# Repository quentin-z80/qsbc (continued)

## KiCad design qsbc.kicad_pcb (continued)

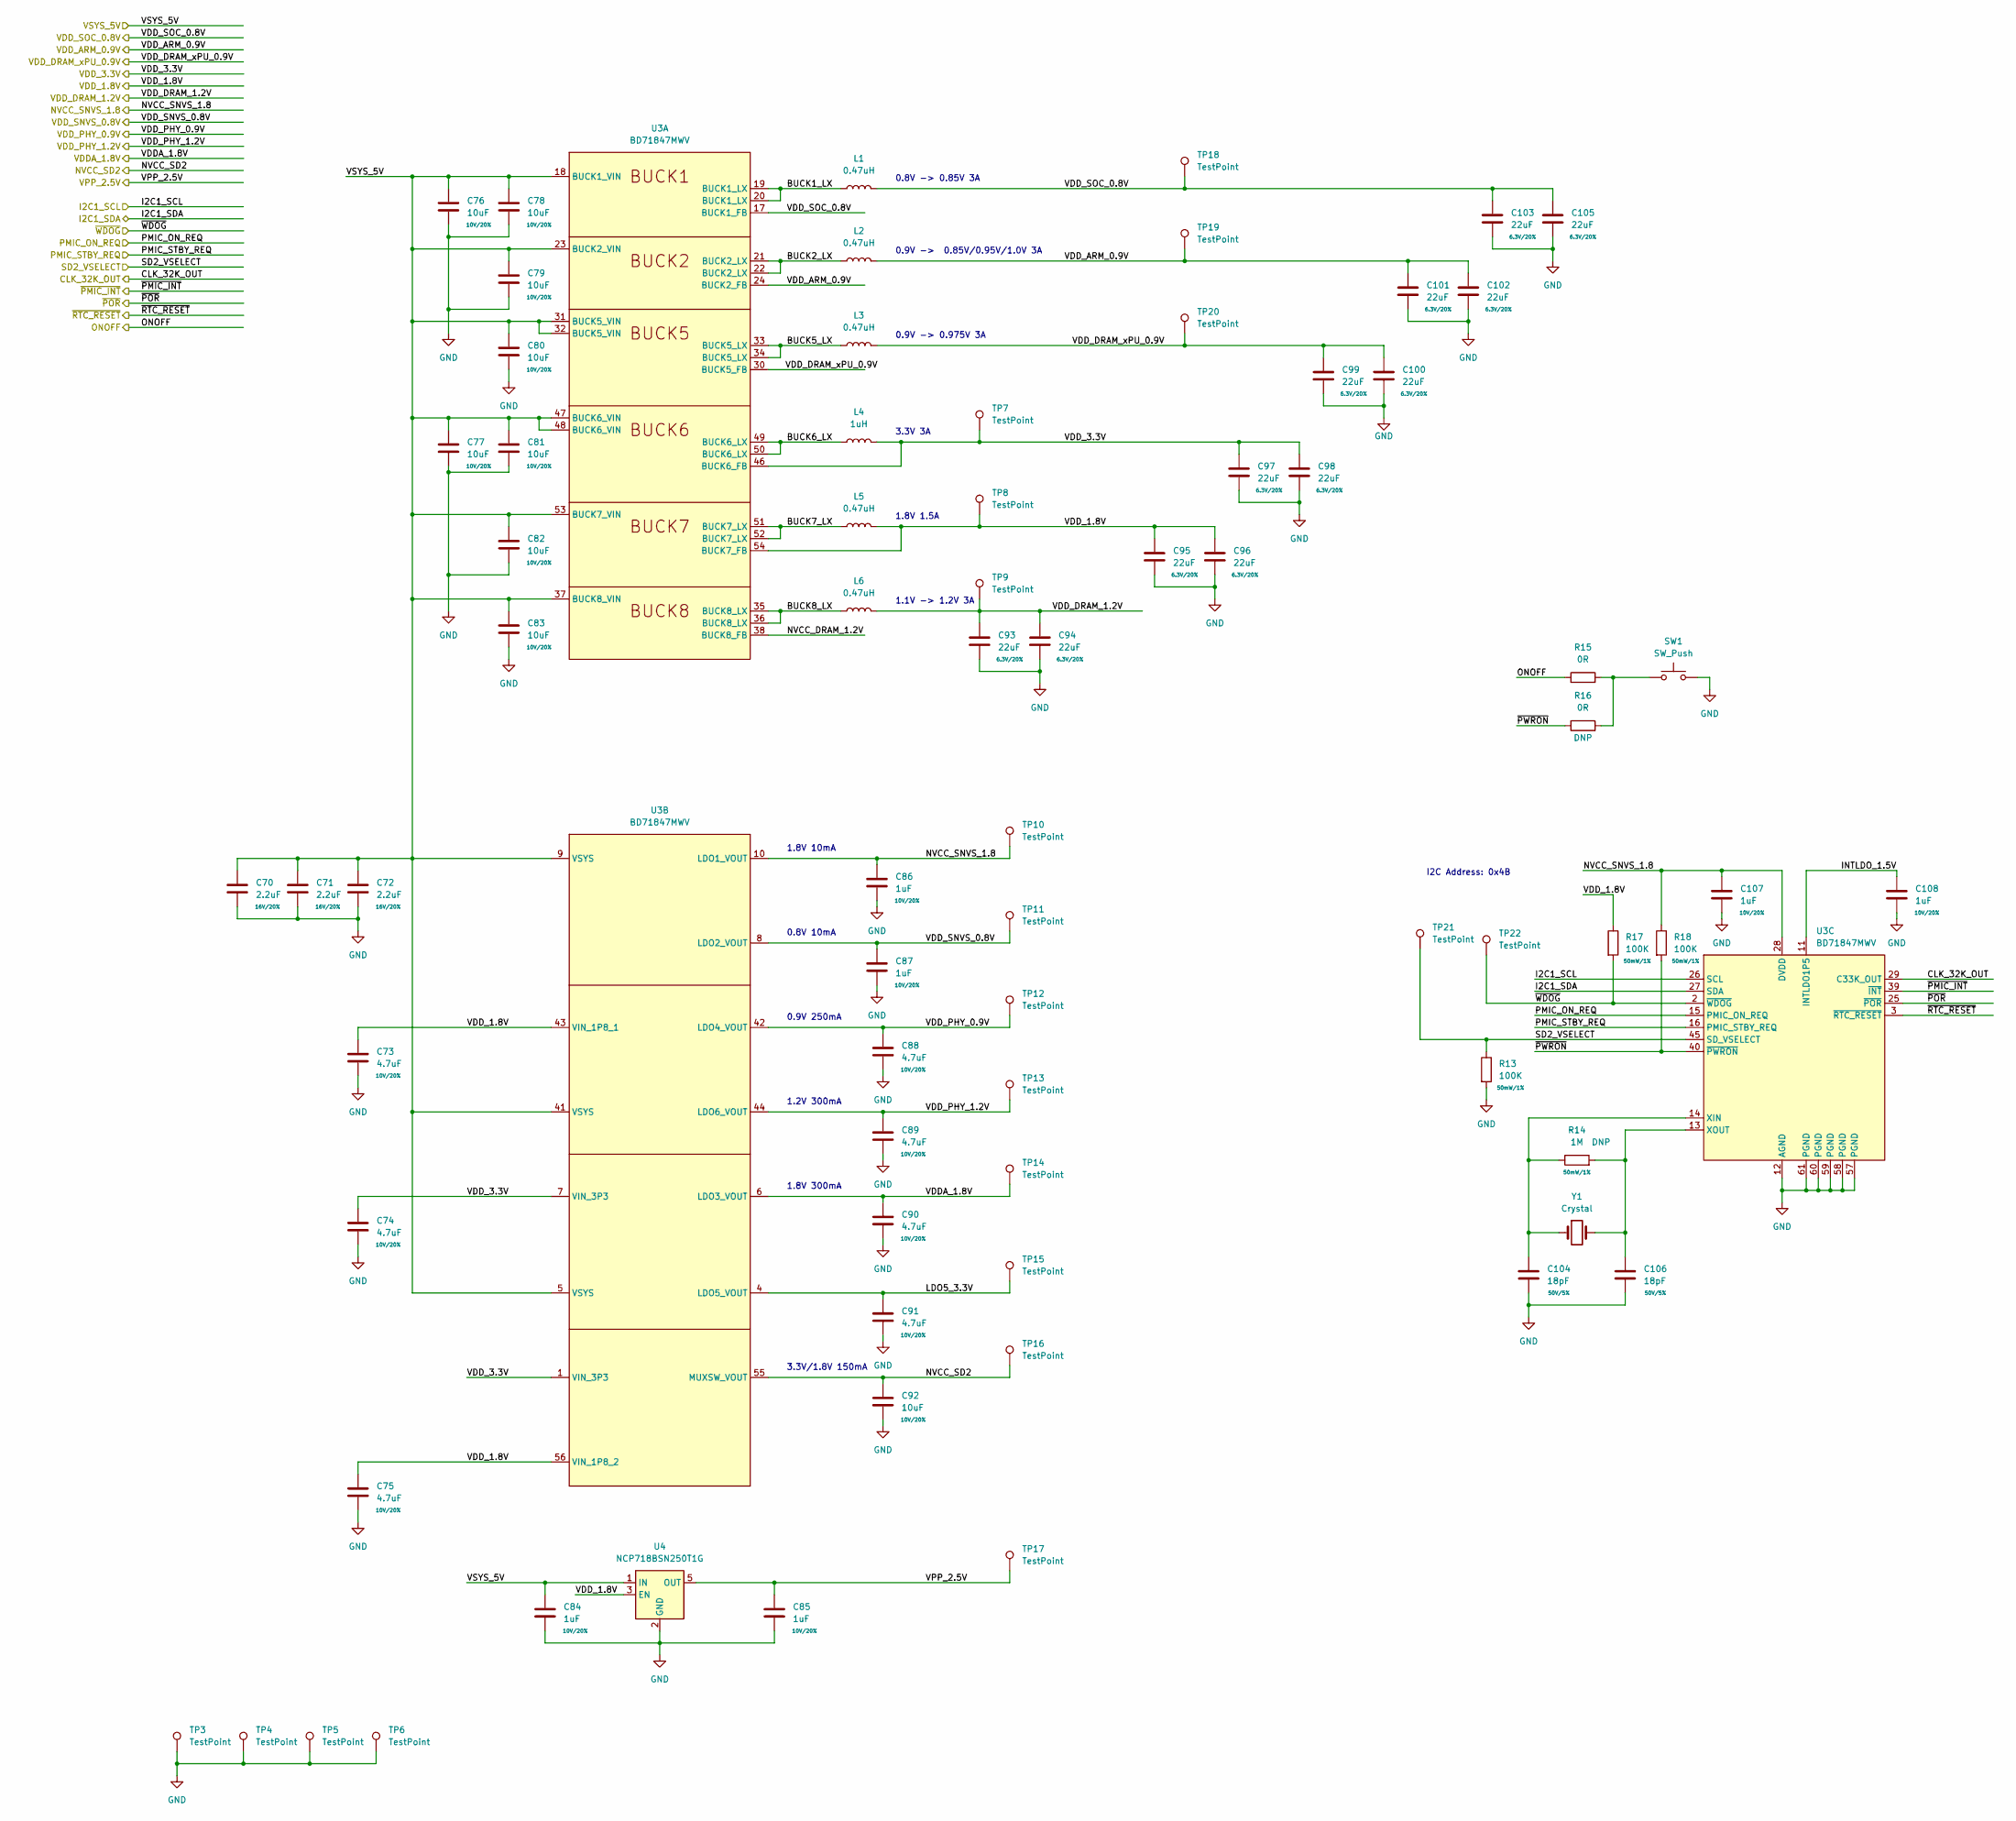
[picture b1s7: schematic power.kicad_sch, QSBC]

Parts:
C70, C71, C72: 2.2uF; C_0402_1005Metric; Rating 16V/20%
C73, C74, C75, C88, C89, C90, C91: 4.7uF; C_0402_1005Metric; Rating 10V/20%
C76, C77, C78, C79, C80, C81, C82, C83, C92: 10uF; C_0603_1608Metric; Rating 10V/20%
C84, C85, C86, C87, C107, C108: 1uF; C_0402_1005Metric; Rating 10V/20%
C93, C94, C95, C96, C97, C98, C99, C100, C101, C102, C103, C105: 22uF; C_0603_1608Metric; Rating 6.3V/20%
C104, C106: 18pF; C_0402_1005Metric; Rating 50V/5%
L1, L2, L3, L5, L6: 0.47uH; L_1008_2520Metric
L4: 1uH; L_1008_2520Metric
R13, R17, R18: 100K; R_0402_1005Metric; Rating 50mW/1%
R14: 1M; R_0402_1005Metric; Rating 50mW/1%
R15, R16: 0R; R_0402_1005Metric
SW1: SW_Push; SW_Tactile_SPST_Angled_PTS645Vx58-2LFS
TP3, TP4, TP5, TP6, TP7, TP8, TP9, TP10, TP11, TP12, TP13, TP14, TP15, TP16, TP17, TP18, TP19, TP20, TP21, TP22: TestPoint; TestPoint_Pad_D1.0mm
U3: BD71847MWV; UQFN56BV7070
U4: NCP718BSN250T1G; SOT-23-5
Y1: Crystal; Crystal_SMD_2012-2Pin_2.0x1.2mm

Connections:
/DDR/VDD_DRAM_1.2V: C93.1, C94.1, L6.2, TP9.1; also elsewhere on the board
/DDR/VPP_2.5V: C85.1, TP17.1, U4.5 (OUT); also elsewhere on the board
/Misc/CLK_32K_OUT: U3.29 (C33K_OUT); also elsewhere on the board
/Misc/NVCC_SNVS_1.8V: C86.1, C107.1, R18.1, TP10.1, U3.10 (LDO1_VOUT), U3.28 (DVDD); also elsewhere on the board
/Misc/ONOFF: R15.1; also elsewhere on the board
/Misc/PMIC_ON_REQ: U3.15 (PMIC_ON_REQ); also elsewhere on the board
/Misc/PMIC_STBY_REQ: U3.16 (PMIC_STBY_REQ); also elsewhere on the board
/Misc/VDD_SNVS_0.8V: C87.1, TP11.1, U3.8 (LDO2_VOUT); also elsewhere on the board
/Misc/~POR: U3.25 (~POR); also elsewhere on the board
/Misc/~RTC_RESET: U3.3 (~RTC_RESET); also elsewhere on the board
/Peripherals/I2C1_SCL: U3.26 (SCL); also elsewhere on the board
/Peripherals/I2C1_SDA: U3.27 (SDA); also elsewhere on the board
/Peripherals/SD2_VSELECT: R13.1, TP21.1, U3.45 (SD_VSELECT); also elsewhere on the board
/Peripherals/~PMIC_INT: U3.39 (~INT); also elsewhere on the board
/Power/BUCK1_LX: L1.1, U3.19 (BUCK1_LX), U3.20 (BUCK1_LX)
/Power/BUCK2_LX: L2.1, U3.21 (BUCK2_LX), U3.22 (BUCK2_LX)
/Power/BUCK5_LX: L3.1, U3.33 (BUCK5_LX), U3.34 (BUCK5_LX)
/Power/BUCK6_LX: L4.1, U3.49 (BUCK6_LX), U3.50 (BUCK6_LX)
/Power/BUCK7_LX: L5.1, U3.51 (BUCK7_LX), U3.52 (BUCK7_LX)
/Power/BUCK8_LX: L6.1, U3.35 (BUCK8_LX), U3.36 (BUCK8_LX)
/Power/INTLDO_1.5V: C108.1, U3.11 (INTLDO1P5)
/Power/LDO5_3.3V: C91.1, TP15.1, U3.4 (LDO5_VOUT)
/Power/NVCC_DRAM_1.2V: U3.38 (BUCK8_FB)
/Power/NVCC_SD2: C92.1, TP16.1, U3.55 (MUXSW_VOUT); also elsewhere on the board
/Power/VDDA_1.8V: C90.1, TP14.1, U3.6 (LDO3_VOUT); also elsewhere on the board
/Power/VDD_ARM_0.9V: C101.1, C102.1, L2.2, TP19.1, U3.24 (BUCK2_FB); also elsewhere on the board
/Power/VDD_DRAM_xPU_0.9V: C99.1, C100.1, L3.2, TP20.1, U3.30 (BUCK5_FB); also elsewhere on the board
/Power/VDD_PHY_0.9V: C88.1, TP12.1, U3.42 (LDO4_VOUT); also elsewhere on the board
/Power/VDD_PHY_1.2V: C89.1, TP13.1, U3.44 (LDO6_VOUT); also elsewhere on the board
/Power/VDD_SOC_0.8V: C103.1, C105.1, L1.2, TP18.1, U3.17 (BUCK1_FB); also elsewhere on the board
/Power/VSYS_5V: C70.1, C71.1, C72.1, C76.1, C77.1, C78.1, C79.1, C80.1, C81.1, C82.1, C83.1, C84.1, U3.5 (VSYS), U3.9 (VSYS), U3.18 (BUCK1_VIN), U3.23 (BUCK2_VIN), U3.31 (BUCK5_VIN), U3.32 (BUCK5_VIN), U3.37 (BUCK8_VIN), U3.41 (VSYS), U3.47 (BUCK6_VIN), U3.48 (BUCK6_VIN), U3.53 (BUCK7_VIN), U4.1 (IN); also elsewhere on the board
/Power/~PWRON: R16.1, R18.2, U3.40 (~PWRON)
/Power/~WDOG: R17.2, TP22.1, U3.2 (~WDOG)
GND: C70.2, C71.2, C72.2, C73.2, C74.2, C75.2, C76.2, C77.2, C78.2, C79.2, C80.2, C81.2, C82.2, C83.2, C84.2, C85.2, C86.2, C87.2, C88.2, C89.2, C90.2, C91.2, C92.2, C93.2, C94.2, C95.2, C96.2, C97.2, C98.2, C99.2, C100.2, C101.2, C102.2, C103.2, C104.2, C105.2, C106.2, C107.2, C108.2, R13.2, SW1.2, TP3.1, TP4.1, TP5.1, TP6.1, U3.12 (AGND), U3.57 (PGND), U3.58 (PGND), U3.59 (PGND), U3.60 (PGND), U3.61 (PGND), U4.2 (GND); also elsewhere on the board
unnamed: C104.1, R14.1, U3.14 (XIN), Y1.1
unnamed: C106.1, R14.2, U3.13 (XOUT), Y1.2
unnamed: R15.2, R16.2, SW1.1
VDD_1.8V: C73.1, C75.1, C95.1, C96.1, L5.2, R17.1, TP8.1, U3.43 (VIN_1P8_1), U3.54 (BUCK7_FB), U3.56 (VIN_1P8_2), U4.3 (EN); also elsewhere on the board
VDD_3.3V: C74.1, C97.1, C98.1, L4.2, TP7.1, U3.1 (VIN_3P3), U3.7 (VIN_3P3), U3.46 (BUCK6_FB); also elsewhere on the board

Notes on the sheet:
0.8V 10mA
1.2V 300mA
0.9V 250mA
I2C Address: 0x4B
0.9V -> 0.85V/0.95V/1.0V 3A
3.3V 3A
0.9V -> 0.975V 3A
1.8V 300mA
1.8V 1.5A
1.8V 10mA
3.3V/1.8V 150mA
1.1V -> 1.2V 3A
0.8V -> 0.85V 3A

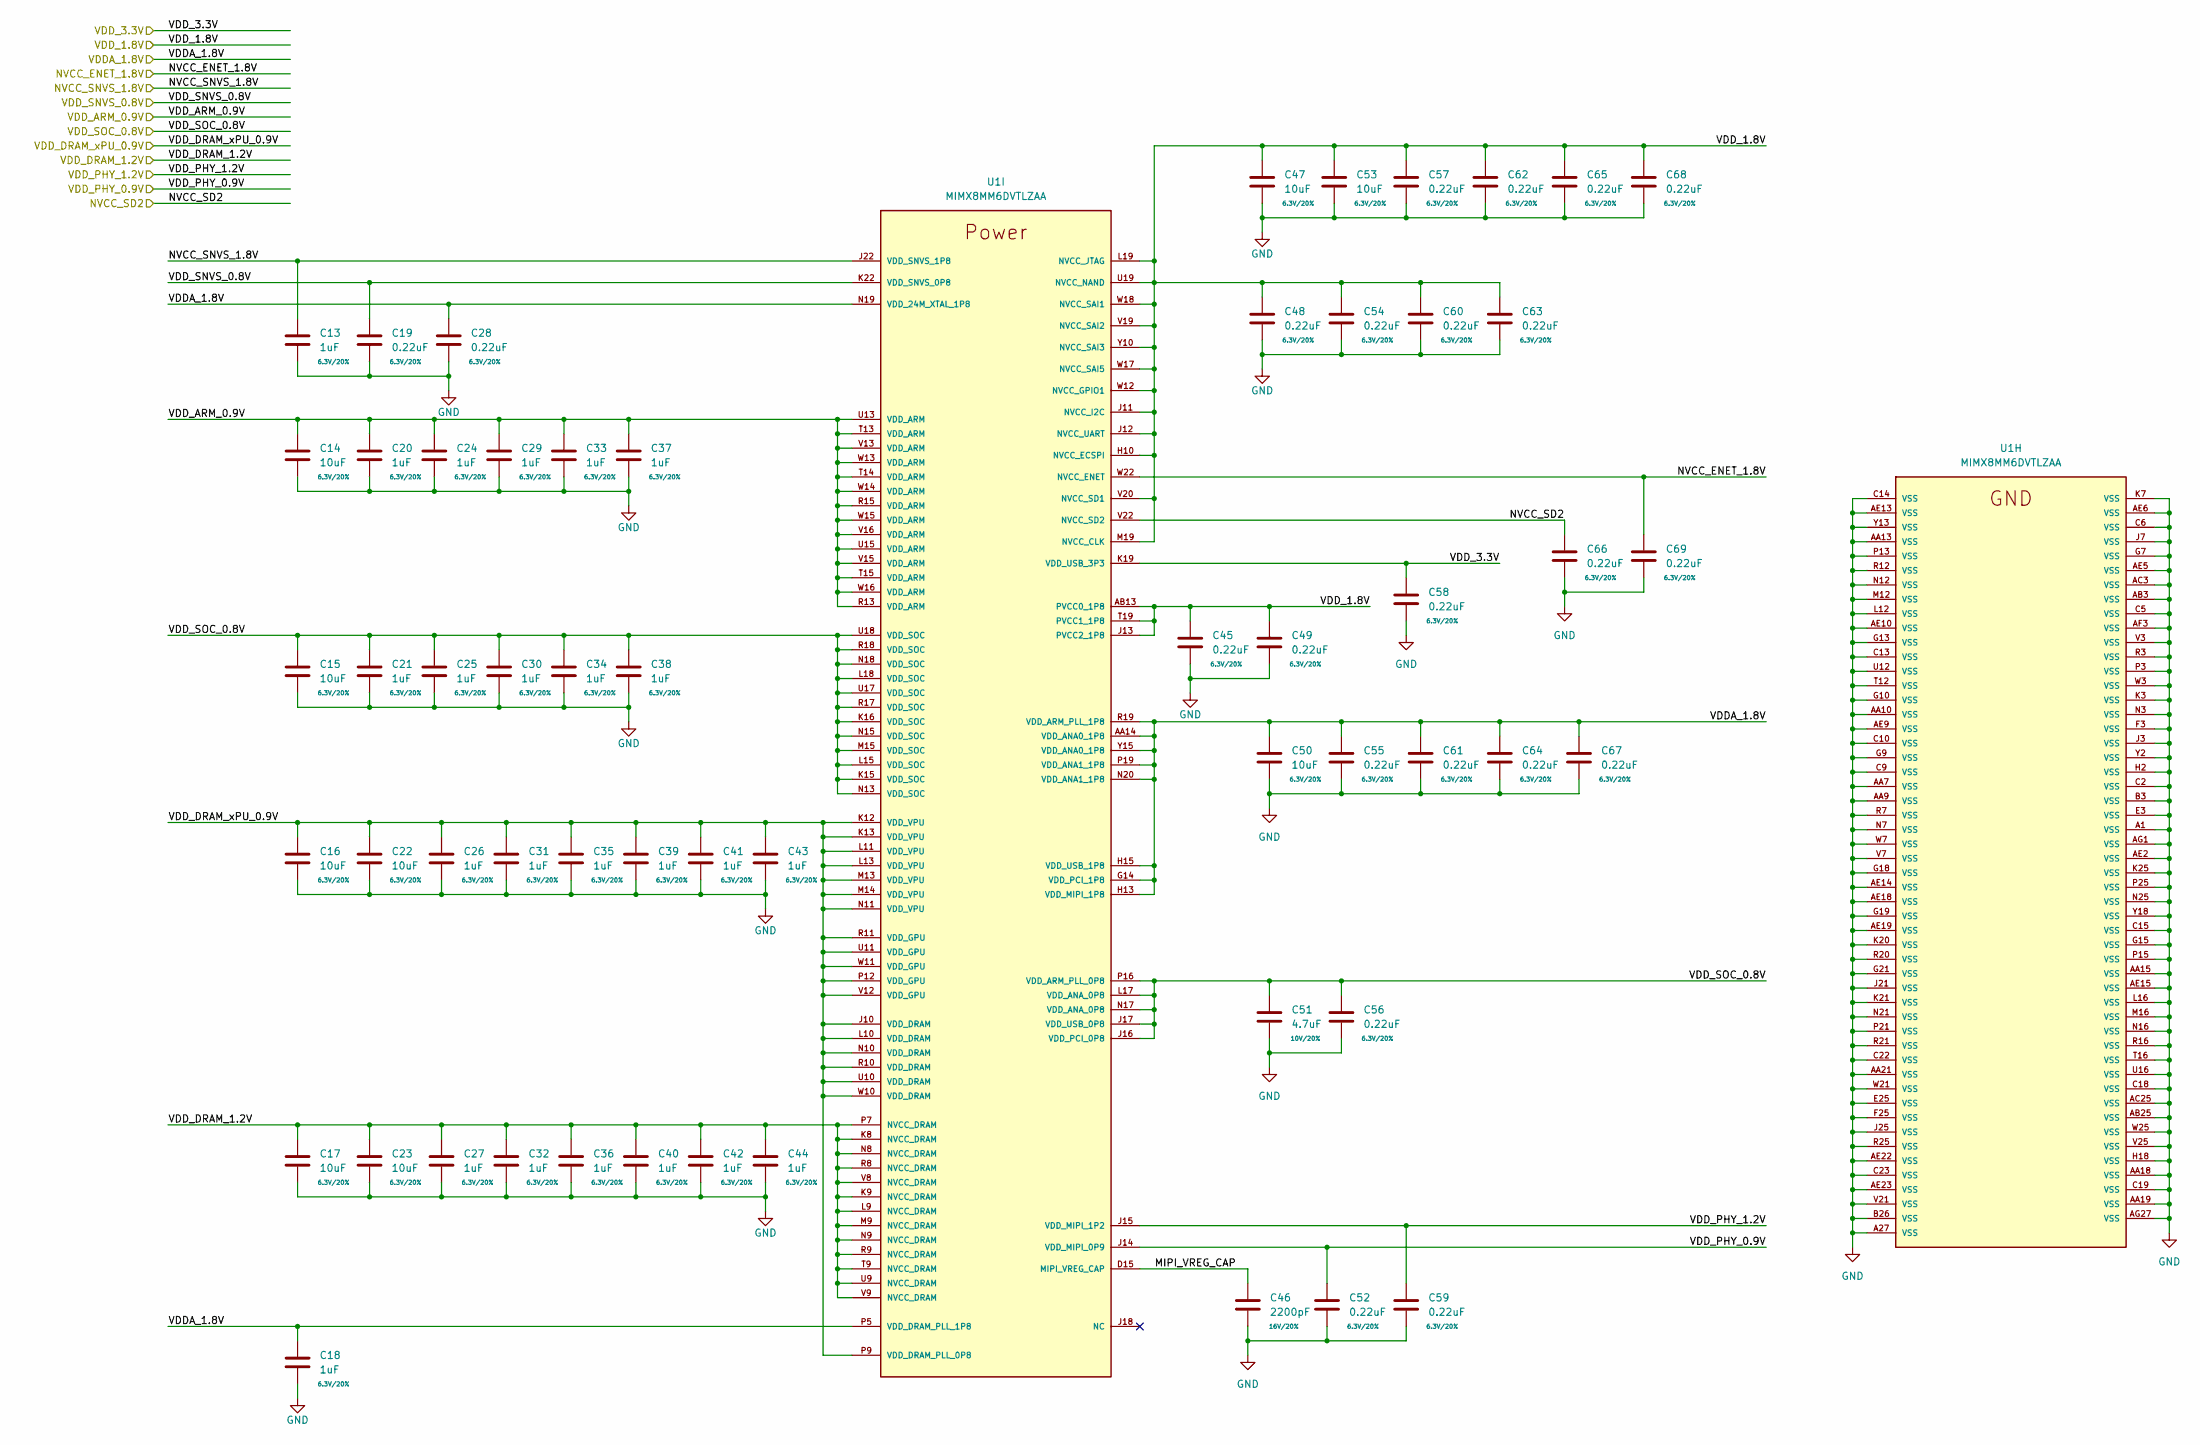
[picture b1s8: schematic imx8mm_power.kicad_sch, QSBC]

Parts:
C13, C18, C20, C21, C24, C25, C26, C27, C29, C30, C31, C32, C33, C34, C35, C36, C37, C38, C39, C40, C41, C42, C43, C44: 1uF; C_0201_0603Metric; Rating 6.3V/20%
C14, C15, C16, C17, C22, C23, C47, C50, C53: 10uF; C_0402_1005Metric; Rating 6.3V/20%
C19, C28, C45, C48, C49, C52, C54, C55, C56, C57, C58, C59, C60, C61, C62, C63, C64, C65, C66, C67, C68, C69: 0.22uF; C_0201_0603Metric; Rating 6.3V/20%
C46: 2200pF; C_0402_1005Metric; Rating 16V/20%
C51: 4.7uF; C_0402_1005Metric; Rating 10V/20%
U1: MIMX8MM6DVTLZAA; SOT1967-1

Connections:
/DDR/VDD_DRAM_1.2V: C17.1, C23.1, C27.1, C32.1, C36.1, C40.1, C42.1, C44.1, U1.K8 (NVCC_DRAM), U1.K9 (NVCC_DRAM), U1.L9 (NVCC_DRAM), U1.M9 (NVCC_DRAM), U1.N8 (NVCC_DRAM), U1.N9 (NVCC_DRAM), U1.P7 (NVCC_DRAM), U1.R8 (NVCC_DRAM), U1.R9 (NVCC_DRAM), U1.T9 (NVCC_DRAM), U1.U9 (NVCC_DRAM), U1.V8 (NVCC_DRAM), U1.V9 (NVCC_DRAM); also elsewhere on the board
/Ethernet/NVCC_ENET_1.8V: C69.1, U1.W22 (NVCC_ENET); also elsewhere on the board
/Misc/NVCC_SNVS_1.8V: C13.1, U1.J22 (VDD_SNVS_1P8); also elsewhere on the board
/Misc/VDD_SNVS_0.8V: C19.1, U1.K22 (VDD_SNVS_0P8); also elsewhere on the board
/Power/NVCC_SD2: C66.1, U1.V22 (NVCC_SD2); also elsewhere on the board
/Power/VDDA_1.8V: C18.1, C28.1, C50.1, C55.1, C61.1, C64.1, C67.1, U1.AA14 (VDD_ANA0_1P8), U1.G14 (VDD_PCI_1P8), U1.H13 (VDD_MIPI_1P8), U1.H15 (VDD_USB_1P8), U1.N19 (VDD_24M_XTAL_1P8), U1.N20 (VDD_ANA1_1P8), U1.P5 (VDD_DRAM_PLL_1P8), U1.P19 (VDD_ANA1_1P8), U1.R19 (VDD_ARM_PLL_1P8), U1.Y15 (VDD_ANA0_1P8); also elsewhere on the board
/Power/VDD_ARM_0.9V: C14.1, C20.1, C24.1, C29.1, C33.1, C37.1, U1.R13 (VDD_ARM), U1.R15 (VDD_ARM), U1.T13 (VDD_ARM), U1.T14 (VDD_ARM), U1.T15 (VDD_ARM), U1.U13 (VDD_ARM), U1.U15 (VDD_ARM), U1.V13 (VDD_ARM), U1.V15 (VDD_ARM), U1.V16 (VDD_ARM), U1.W13 (VDD_ARM), U1.W14 (VDD_ARM), U1.W15 (VDD_ARM), U1.W16 (VDD_ARM); also elsewhere on the board
/Power/VDD_DRAM_xPU_0.9V: C16.1, C22.1, C26.1, C31.1, C35.1, C39.1, C41.1, C43.1, U1.J10 (VDD_DRAM), U1.K12 (VDD_VPU), U1.K13 (VDD_VPU), U1.L10 (VDD_DRAM), U1.L11 (VDD_VPU), U1.L13 (VDD_VPU), U1.M13 (VDD_VPU), U1.M14 (VDD_VPU), U1.N10 (VDD_DRAM), U1.N11 (VDD_VPU), U1.P9 (VDD_DRAM_PLL_0P8), U1.P12 (VDD_GPU), U1.R10 (VDD_DRAM), U1.R11 (VDD_GPU), U1.U10 (VDD_DRAM), U1.U11 (VDD_GPU), U1.V12 (VDD_GPU), U1.W10 (VDD_DRAM), U1.W11 (VDD_GPU); also elsewhere on the board
/Power/VDD_PHY_0.9V: C52.1, U1.J14 (VDD_MIPI_0P9); also elsewhere on the board
/Power/VDD_PHY_1.2V: C59.1, U1.J15 (VDD_MIPI_1P2); also elsewhere on the board
/Power/VDD_SOC_0.8V: C15.1, C21.1, C25.1, C30.1, C34.1, C38.1, C51.1, C56.1, U1.J16 (VDD_PCI_0P8), U1.J17 (VDD_USB_0P8), U1.K15 (VDD_SOC), U1.K16 (VDD_SOC), U1.L15 (VDD_SOC), U1.L17 (VDD_ANA_0P8), U1.L18 (VDD_SOC), U1.M15 (VDD_SOC), U1.N13 (VDD_SOC), U1.N15 (VDD_SOC), U1.N17 (VDD_ANA_0P8), U1.N18 (VDD_SOC), U1.P16 (VDD_ARM_PLL_0P8), U1.R17 (VDD_SOC), U1.R18 (VDD_SOC), U1.U17 (VDD_SOC), U1.U18 (VDD_SOC); also elsewhere on the board
/i.MX8MM Power/MIPI_VREG_CAP: C46.1, U1.D15 (MIPI_VREG_CAP)
GND: C13.2, C14.2, C15.2, C16.2, C17.2, C18.2, C19.2, C20.2, C21.2, C22.2, C23.2, C24.2, C25.2, C26.2, C27.2, C28.2, C29.2, C30.2, C31.2, C32.2, C33.2, C34.2, C35.2, C36.2, C37.2, C38.2, C39.2, C40.2, C41.2, C42.2, C43.2, C44.2, C45.2, C46.2, C47.2, C48.2, C49.2, C50.2, C51.2, C52.2, C53.2, C54.2, C55.2, C56.2, C57.2, C58.2, C59.2, C60.2, C61.2, C62.2, C63.2, C64.2, C65.2, C66.2, C67.2, C68.2, C69.2, U1.A1 (VSS), U1.A27 (VSS), U1.AA7 (VSS), U1.AA9 (VSS), U1.AA10 (VSS), U1.AA13 (VSS), U1.AA15 (VSS), U1.AA18 (VSS), U1.AA19 (VSS), U1.AA21 (VSS), U1.AB3 (VSS), U1.AB25 (VSS), U1.AC3 (VSS), U1.AC25 (VSS), U1.AE2 (VSS), U1.AE5 (VSS), U1.AE6 (VSS), U1.AE9 (VSS), U1.AE10 (VSS), U1.AE13 (VSS), U1.AE14 (VSS), U1.AE15 (VSS), U1.AE18 (VSS), U1.AE19 (VSS), U1.AE22 (VSS), U1.AE23 (VSS), U1.AF3 (VSS), U1.AG1 (VSS), U1.AG27 (VSS), U1.B3 (VSS), U1.B26 (VSS), U1.C2 (VSS), U1.C5 (VSS), U1.C6 (VSS), U1.C9 (VSS), U1.C10 (VSS), U1.C13 (VSS), U1.C14 (VSS), U1.C15 (VSS), U1.C18 (VSS), U1.C19 (VSS), U1.C22 (VSS), U1.C23 (VSS), U1.E3 (VSS), U1.E25 (VSS), U1.F3 (VSS), U1.F25 (VSS), U1.G7 (VSS), U1.G9 (VSS), U1.G10 (VSS), U1.G13 (VSS), U1.G15 (VSS), U1.G18 (VSS), U1.G19 (VSS), U1.G21 (VSS), U1.H2 (VSS), U1.H18 (VSS), U1.J3 (VSS), U1.J7 (VSS), U1.J21 (VSS), U1.J25 (VSS), U1.K3 (VSS), U1.K7 (VSS), U1.K20 (VSS), U1.K21 (VSS), U1.K25 (VSS), U1.L12 (VSS), U1.L16 (VSS), U1.M12 (VSS), U1.M16 (VSS), U1.N3 (VSS), U1.N7 (VSS), U1.N12 (VSS), U1.N16 (VSS), U1.N21 (VSS), U1.N25 (VSS), U1.P3 (VSS), U1.P13 (VSS), U1.P15 (VSS), U1.P21 (VSS), U1.P25 (VSS), U1.R3 (VSS), U1.R7 (VSS), U1.R12 (VSS), U1.R16 (VSS), U1.R20 (VSS), U1.R21 (VSS), U1.R25 (VSS), U1.T12 (VSS), U1.T16 (VSS), U1.U12 (VSS), U1.U16 (VSS), U1.V3 (VSS), U1.V7 (VSS), U1.V21 (VSS), U1.V25 (VSS), U1.W3 (VSS), U1.W7 (VSS), U1.W21 (VSS), U1.W25 (VSS), U1.Y2 (VSS), U1.Y13 (VSS), U1.Y18 (VSS); also elsewhere on the board
VDD_1.8V: C45.1, C47.1, C48.1, C49.1, C53.1, C54.1, C57.1, C60.1, C62.1, C63.1, C65.1, C68.1, U1.AB13 (PVCC0_1P8), U1.H10 (NVCC_ECSPI), U1.J11 (NVCC_I2C), U1.J12 (NVCC_UART), U1.J13 (PVCC2_1P8), U1.L19 (NVCC_JTAG), U1.M19 (NVCC_CLK), U1.T19 (PVCC1_1P8), U1.U19 (NVCC_NAND), U1.V19 (NVCC_SAI2), U1.V20 (NVCC_SD1), U1.W12 (NVCC_GPIO1), U1.W17 (NVCC_SAI5), U1.W18 (NVCC_SAI1), U1.Y10 (NVCC_SAI3); also elsewhere on the board
VDD_3.3V: C58.1, U1.K19 (VDD_USB_3P3); also elsewhere on the board

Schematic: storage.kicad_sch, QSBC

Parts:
C142: 18pF; C_0201_0603Metric; Rating ??V/??%
C143: 10uF; C_0402_1005Metric; Rating 6.3V/20%
C144, C145, C147: 0.1uF; C_0402_1005Metric; Rating 25V/20%
C146: 1uF; C_0402_1005Metric; Rating 10V/20%
J6: Micro_SD_Card_Det1; GCT_MEM2051-00-195-00-A_REVC
R80, R83, R84: 10K; R_0402_1005Metric; Rating 50mW/1%; MPN RC0402JR-0710KL; DigiKey_PN 311-10KJRCT-ND
R81: 0R; R_0201_0603Metric
R82: 10K; R_0402_1005Metric; Rating 50mW/1%
U1: MIMX8MM6DVTLZAA; SOT1967-1
U25, U29: TPD4EUSB30; USON-10_2.5x1.0mm_P0.5mm
U26: D5V0H1B2LP; DFN100X60X45-2N
U27: W25Q32JWZP; WSON-8-1EP_6x5mm_P1.27mm_EP3.4x4.3mm
U28: SiP32431DR3; SOT-363_SC-70-6

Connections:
/Power/NVCC_SD2: R80.1, R83.1, R84.1; also elsewhere on the board
/Storage/QSPI_CLK: U1.N22 (NAND_ALE), U27.6 (CLK)
/Storage/QSPI_DATA0: U1.P23 (NAND_DATA00), U27.5 (DI(IO0))
/Storage/QSPI_DATA1: U1.K24 (NAND_DATA01), U27.2 (DO(IO1))
/Storage/QSPI_DATA2: U1.K23 (NAND_DATA02), U27.3 (IO2)
/Storage/QSPI_DATA3: U1.N23 (NAND_DATA03), U27.7 (IO3)
/Storage/SD2_CLK: J6.5 (CLK), R81.2, U29.1 (D1+), U29.10
/Storage/SD2_CLK_R: R81.1, U1.W23 (SD2_CLK)
/Storage/SD2_CMD: J6.3 (CMD), R84.2, U1.W24 (SD2_CMD), U29.2 (D1-), U29.9
/Storage/SD2_DATA0: J6.7 (DAT0), R83.2, U1.AB23 (SD2_DATA0), U25.4 (D2+), U25.7
/Storage/SD2_DATA1: J6.8 (DAT1), U1.AB24 (SD2_DATA1), U25.2 (D1-), U25.9
/Storage/SD2_DATA2: J6.1 (DAT2), U1.V24 (SD2_DATA2), U29.4 (D2+), U29.7
/Storage/SD2_DATA3: J6.2 (DAT3/CD), U1.V23 (SD2_DATA3), U25.5 (D2-), U25.6
/Storage/VDD_SD2: C143.1, C144.1, C147.1, J6.4 (VDD), U26.2, U28.1 (OUT)
/Storage/~QSPI_CS: R82.2, U1.N24 (NAND_CE0_B), U27.1 (~CS)
/Storage/~SD2_CD: J6.10 (DET), U1.AA26 (SD2_CD_B), U25.1 (D1+), U25.10
/Storage/~SD2_RESET: R80.2, U1.AB26 (SD2_RESET_B), U28.3 (ON)
GND: C142.2, C143.2, C144.2, C145.2, C146.2, C147.2, J6.6 (VSS), J6.9 (SHIELD), U25.3 (GND), U25.8 (GND), U26.1, U27.4 (GND), U27.9 (EP), U28.2 (GND), U28.5 (GND), U29.3 (GND), U29.8 (GND); also elsewhere on the board
unnamed: C142.1, U1.R22 (NAND_DQS)
VDD_1.8V: C145.1, R82.1, U27.8 (VCC); also elsewhere on the board
VDD_3.3V: C146.1, U28.4 (IN); also elsewhere on the board

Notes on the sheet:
TODO: Find Best Value

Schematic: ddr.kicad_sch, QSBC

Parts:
C1: 0.22uF; C_0201_0603Metric; Rating 10V/20%
C2, C3, C4, C5, C8, C9, C10, C11: 4.7uF; C_0402_1005Metric; Rating 10V/20%
C6, C7: 1uF; C_0402_1005Metric; Rating 10V/20%
C12: 0.01uF; C_0201_0603Metric; Rating 6.3V/20%
R1, R10: 240R; R_0201_0603Metric; Rating 50mW/1%
R2, R3, R4: 43R; R_0201_0603Metric; Rating 50mW/1%
R5: 10K; R_0402_1005Metric; Rating 50mW/1%
R6, R7, R8, R9: 0R; R_0201_0603Metric
R11, R12: 1K; R_0402_1005Metric; Rating 50mW/1%
TP1: TestPoint; TestPoint_Pad_D0.4mm
TP2: TestPoint; TestPoint_Pad_D1.0mm
U1: MIMX8MM6DVTLZAA; SOT1967-1
U2: MT40A1G16KD-062E; MICRON-FBGA-96

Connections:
/DDR/DRAM_A00: U1.AD5 (DRAM_AC31), U2.P3 (A0)
/DDR/DRAM_A01: U1.U1 (DRAM_AC25), U2.P7 (A1)
/DDR/DRAM_A02: U1.U2 (DRAM_AC24), U2.R3 (A2)
/DDR/DRAM_A03: U1.N6 (DRAM_AC15), U2.N7 (A3)
/DDR/DRAM_A04: U1.K5 (DRAM_AC14), U2.N3 (A4)
/DDR/DRAM_A05: U1.N5 (DRAM_AC13), U2.P8 (A5)
/DDR/DRAM_A06: U1.N4 (DRAM_AC12), U2.P2 (A6)
/DDR/DRAM_A07: U1.E4 (DRAM_AC10), U2.R8 (A7)
/DDR/DRAM_A08: U1.D5 (DRAM_AC11), U2.R2 (A8)
/DDR/DRAM_A09: U1.J5 (DRAM_AC07), U2.R7 (A9)
/DDR/DRAM_A10: U1.AC4 (DRAM_AC30), U2.M3 (A10/AP)
/DDR/DRAM_A11: U1.K6 (DRAM_AC09), U2.T2 (A11)
/DDR/DRAM_A12: U1.J6 (DRAM_AC08), U2.M7 (A12/BC_N)
/DDR/DRAM_A13: U1.W6 (DRAM_AC28), U2.T8 (A13)
/DDR/DRAM_A14: U1.T1 (DRAM_AC34), U2.L2 (WE_N/A14)
/DDR/DRAM_A15: U1.R5 (DRAM_AC33), U2.M8 (CAS_N/A15)
/DDR/DRAM_A16: U1.T2 (DRAM_AC35), U2.L8 (RAS_N/A16)
/DDR/DRAM_BA0: U1.V6 (DRAM_AC29), U2.N2 (BA0)
/DDR/DRAM_BA1: U1.N1 (DRAM_AC26), U2.N8 (BA1)
/DDR/DRAM_BG0: U1.L2 (DRAM_AC04), U2.M2 (BG0)
/DDR/DRAM_BG1: R6.1, U1.L1 (DRAM_AC05)
/DDR/DRAM_CKE: U1.F4 (DRAM_AC00), U2.K2 (CKE)
/DDR/DRAM_CK_N: R2.2, U1.M2 (DRAM_AC17), U2.K8 (CK_C)
/DDR/DRAM_CK_P: R3.2, U1.M1 (DRAM_AC16), U2.K7 (CK_T)
/DDR/DRAM_D00: U1.A5 (DRAM_DQ00), U2.G2 (LDQ0)
/DDR/DRAM_D01: U1.B5 (DRAM_DQ01), U2.H2 (LDQ4)
/DDR/DRAM_D02: U1.D2 (DRAM_DQ02), U2.H7 (LDQ3)
/DDR/DRAM_D03: U1.D1 (DRAM_DQ03), U2.H8 (LDQ5)
/DDR/DRAM_D04: U1.C1 (DRAM_DQ04), U2.F7 (LDQ1)
/DDR/DRAM_D05: U1.B1 (DRAM_DQ05), U2.J7 (LDQ7)
/DDR/DRAM_D06: U1.A3 (DRAM_DQ06), U2.J3 (LDQ6)
/DDR/DRAM_D07: U1.B4 (DRAM_DQ07), U2.H3 (LDQ2)
/DDR/DRAM_D08: U1.F2 (DRAM_DQ08), U2.C3 (UDQ10)
/DDR/DRAM_D09: U1.G2 (DRAM_DQ09), U2.D3 (UDQ14)
/DDR/DRAM_D10: U1.J1 (DRAM_DQ10), U2.C7 (UDQ11)
/DDR/DRAM_D11: U1.J2 (DRAM_DQ11), U2.B8 (UDQ9)
/DDR/DRAM_D12: U1.K2 (DRAM_DQ12), U2.C8 (UDQ13)
/DDR/DRAM_D13: U1.K1 (DRAM_DQ13), U2.D7 (UDQ15)
/DDR/DRAM_D14: U1.E1 (DRAM_DQ14), U2.C2 (UDQ12)
/DDR/DRAM_D15: U1.E2 (DRAM_DQ15), U2.A3 (UDQ8)
/DDR/DRAM_DMI0: U1.A4 (DRAM_DM0), U2.E7 (NF/LDBI_N/LDM_N)
/DDR/DRAM_DMI1: U1.F1 (DRAM_DM1), U2.E2 (NF/UDBI_N/UDM_N)
/DDR/DRAM_DQS0_N: U1.B2 (DRAM_DQS0_N), U2.F3 (LDQS_C)
/DDR/DRAM_DQS0_P: U1.A2 (DRAM_DQS0_P), U2.G3 (LDQS_T)
/DDR/DRAM_DQS1_N: U1.H1 (DRAM_DQS1_N), U2.A7 (UDQS_C)
/DDR/DRAM_DQS1_P: U1.G1 (DRAM_DQS1_P), U2.B7 (UDQS_T)
/DDR/DRAM_ODT: U1.V5 (DRAM_AC36), U2.K3 (ODT)
/DDR/DRAM_PARITY: U1.R6 (DRAM_AC27), U2.T3 (PAR)
/DDR/DRAM_VREF: C6.2, C7.1, C12.1, R11.1, R12.2, TP2.1, U2.M1 (VREFCA)
/DDR/DRAM_ZN: R1.2, U1.P2 (DRAM_ZN)
/DDR/PHY_VREF: TP1.1, U1.P1 (DRAM_VREF)
/DDR/VDD_DRAM_1.2V: C2.1, C3.1, C4.1, C5.1, C6.1, C8.1, C10.1, R4.2, R11.2, U2.A1 (VDDQ1), U2.A9 (VDDQ2), U2.B3 (VDD1), U2.B9 (VDD2), U2.C1 (VDDQ3), U2.D1 (VDD3), U2.D9 (VDDQ4), U2.F2 (VDDQ5), U2.F8 (VDDQ6), U2.G1 (VDDQ7), U2.G7 (VDD4), U2.G9 (VDDQ8), U2.J1 (VDD5), U2.J2 (VDDQ9), U2.J8 (VDDQ10), U2.J9 (VDD6), U2.L1 (VDD7), U2.L9 (VDD8), U2.R1 (VDD9), U2.T9 (VDD10); also elsewhere on the board
/DDR/VPP_2.5V: C9.1, C11.1, U2.B1 (VPP1), U2.R9 (VPP2); also elsewhere on the board
/DDR/~DRAM_ACT: U1.F6 (DRAM_AC06), U2.L3 (ACT_N)
/DDR/~DRAM_ALERT: R4.1, U1.R2 (DRAM_ALERT_N), U2.P9 (ALERT_N)
/DDR/~DRAM_CS0: U1.K4 (DRAM_AC02), U2.L7 (CS_N)
/DDR/~DRAM_RESET: R5.2, U1.R1 (DRAM_RESET_N), U2.P1 (RESET_N)
GND: C1.2, C2.2, C3.2, C4.2, C5.2, C7.2, C8.2, C9.2, C10.2, C11.2, C12.2, R1.1, R5.1, R7.2, R8.2, R9.2, R10.1, R12.1, U2.A2 (VSSQ1), U2.A8 (VSSQ2), U2.B2 (VSS1), U2.C9 (VSSQ3), U2.D2 (VSSQ4), U2.D8 (VSSQ5), U2.E1 (VSS2), U2.E3 (VSSQ6), U2.E8 (VSSQ7), U2.F1 (VSSQ8), U2.G8 (VSS3), U2.H1 (VSSQ9), U2.H9 (VSSQ10), U2.K1 (VSS4), U2.K9 (VSS5), U2.N1 (VSS6), U2.N9 (TEN), U2.T1 (VSS7); also elsewhere on the board
unnamed: C1.1, R2.1, R3.1
unnamed: R6.2, R7.1, U2.M9 (VSS8)
unnamed: R8.1, U2.E9 (VSS9)
unnamed: R9.1, U2.T7 (NF/NC)
unnamed: R10.2, U2.F9 (ZQ)

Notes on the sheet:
240R
Single Die
Type
DNP
Dual Die

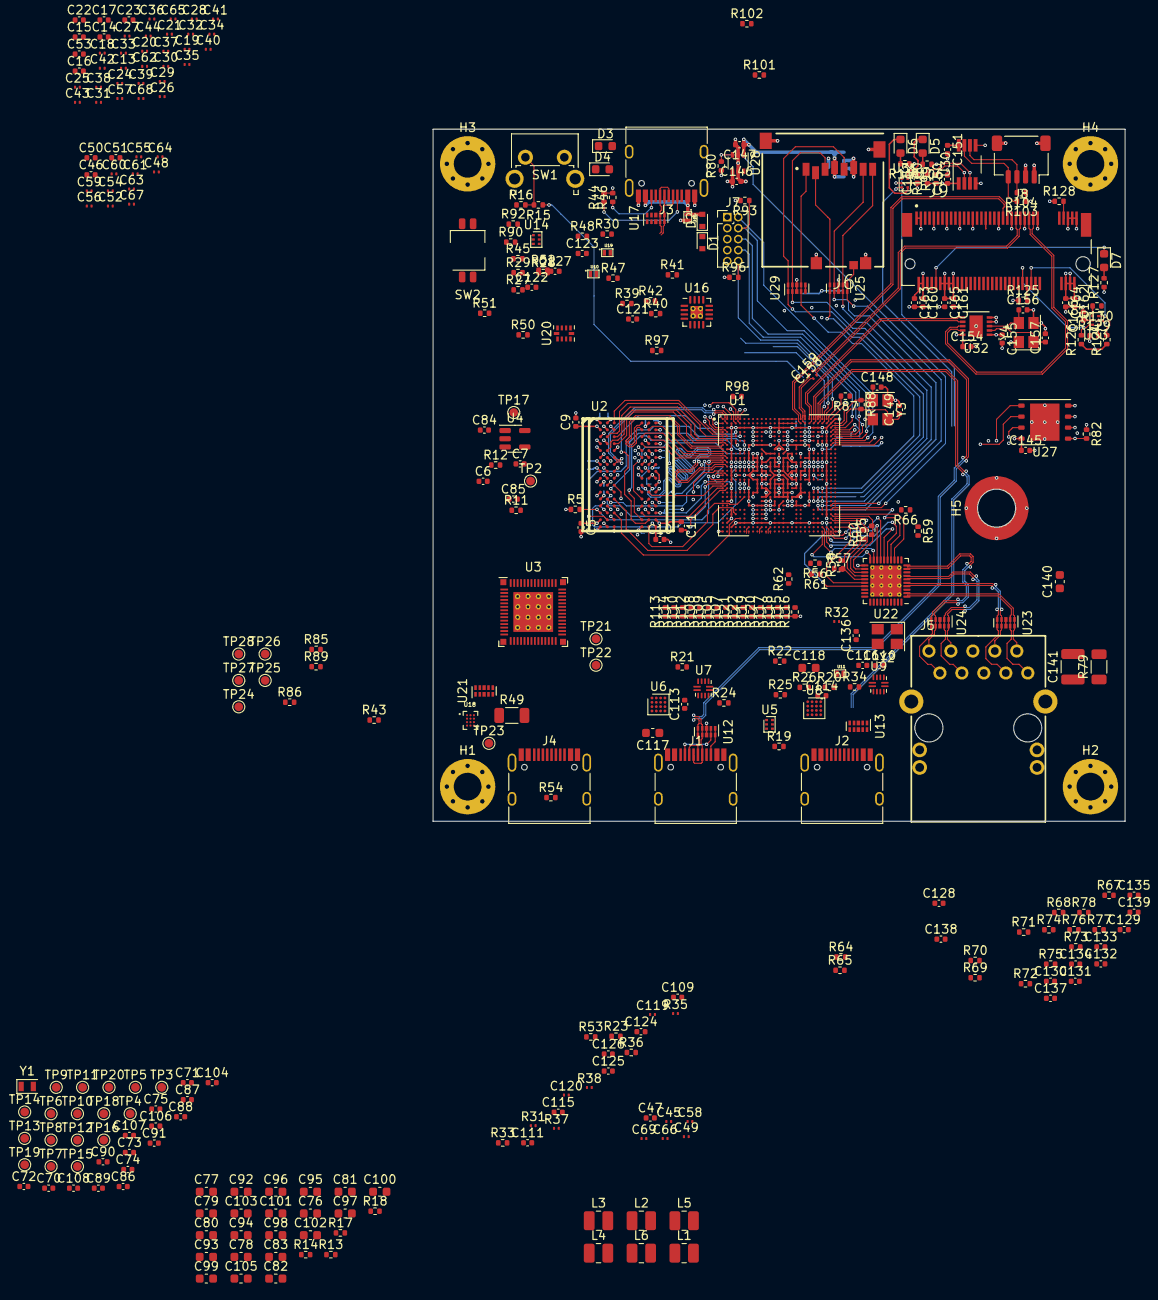
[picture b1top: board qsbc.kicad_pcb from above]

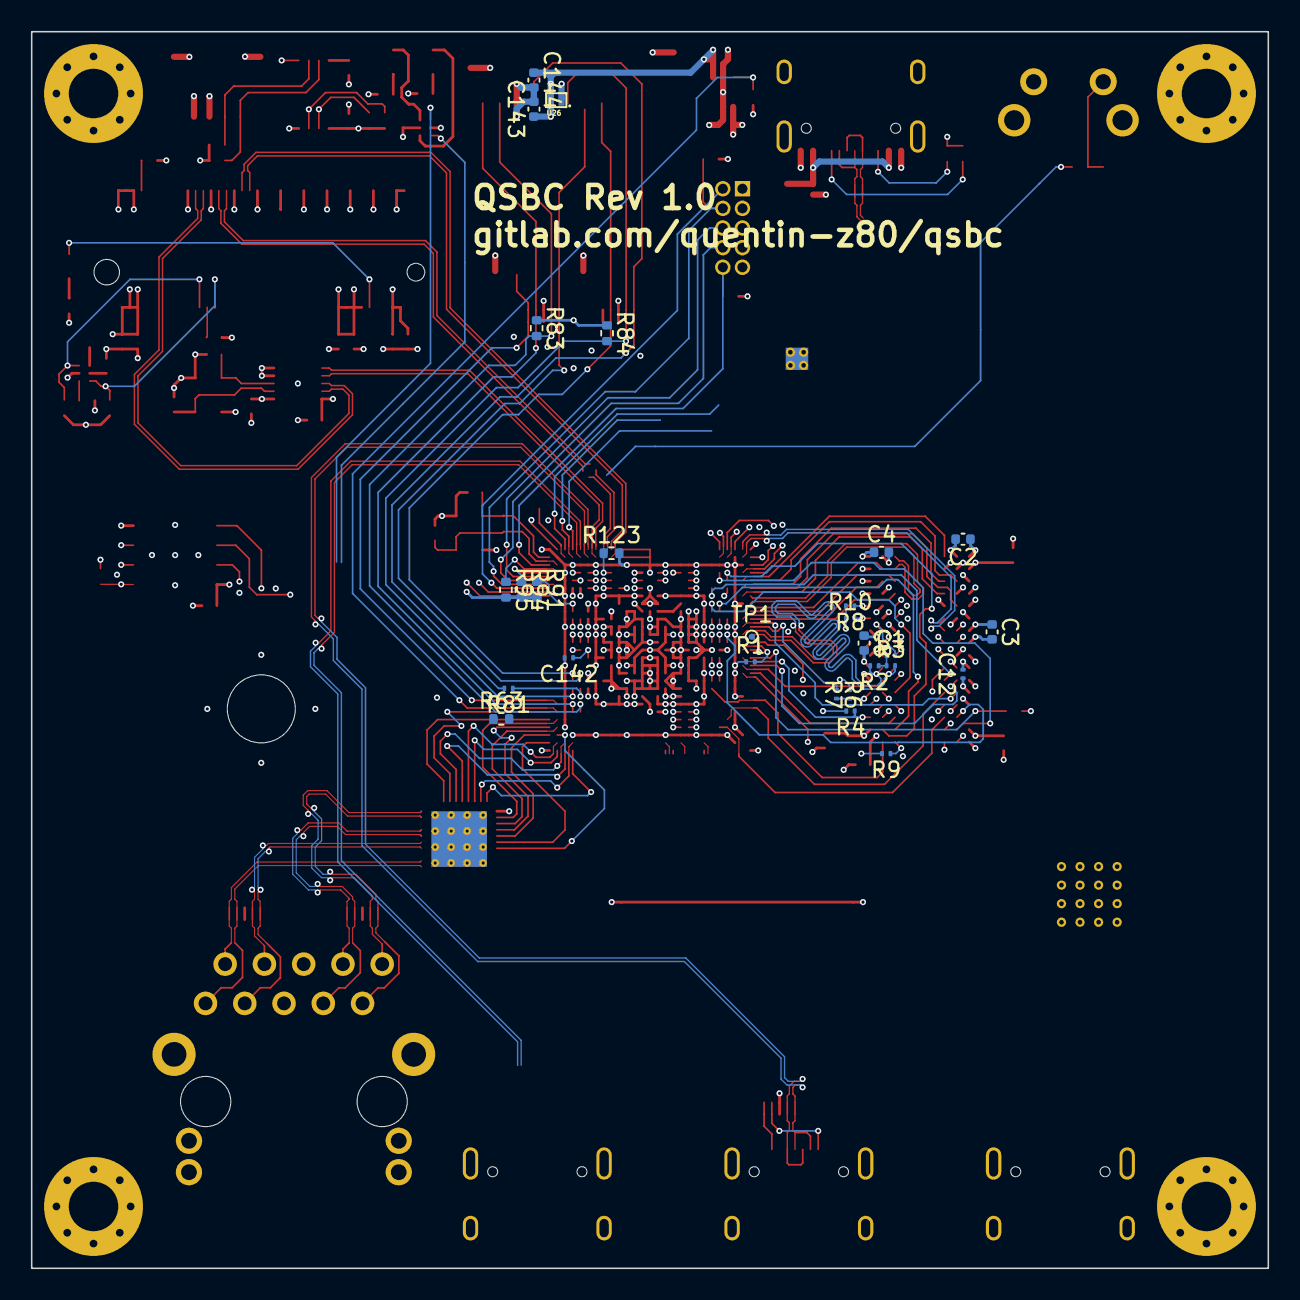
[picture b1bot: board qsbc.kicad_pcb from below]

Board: 8 copper layers, 80.0 x 80.0 mm, 388 parts (28 on the bottom side), 281 nets.

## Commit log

2022-05-07 inital commit
2022-05-08 move to i.MX8M Mini
2022-05-08 ddr sch done
2022-06-04 misc work, usb sch done
2022-06-26 enet sch done, other misc sch work
2022-06-26 enet: add hierarchial labels
2022-07-01 pcie done, misc fixes for usb, enet
2022-07-02 storage done, peri work, misc fixes
2022-07-09 ddr: add dual die support, misc work
2022-07-09 fix ref desgigators, add table for dram config
2022-07-09 add ddr vpp ldo, fix ddr net names
2022-07-26 add inital ddr tool version, lots of routing work
2022-08-01 v2 of ddr flytimes tool, lots of routing work, sch fixes
2022-08-06 more routing work, prepare to change to x32 lpddr4
2022-08-07 inital routing of ddr data bus, sch work
2022-08-26 README.md: update specs
2022-08-26 README.md: specs: add m.2 slot
2022-09-09 add SN65DSI86 DSI2DP ic, SCH, PCB work, flytime work
2022-09-10 add UART4 connector
2022-09-18 change USB-UART conn, add new 0402 fp, more pcb work
2022-09-18 place imx8mm/lpddr4 decoupling caps, lib cleanup
2022-09-18 fix lpddr4 3d model
2022-09-25 place / route SOC/DDR decoupling caps
2022-09-25 swap usb ctrl signals for layout
2022-10-01 usb-c routing done, decoupling caps work
2022-10-08 pmic routing almost done
2022-10-08 most of routing done
2022-10-09 fix all drc errors / warnings
2022-10-09 finish l3 zones
2022-10-09 v2 of flytime tool
2022-10-16 misc length matching, cleanup files
2022-10-17 DDR_A length matching done
2022-10-24 more delay matching, update drc rules for better clearance
2022-11-02 length matched DDR_A addr, cmd, ctrl, and byte 0
2022-11-02 length matched DDR_A byte 1
2022-11-03 length matched DDR_B byte 1
2022-11-03 length matched DDR_B byte 0
2022-11-03 fix some drc errors in ddr area
2022-11-03 small sch fixes / cleanup
2022-11-05 bom work, change uart level shifter and m.2 socket
2022-11-05 fix missing power connection
2022-11-05 add gnd zones to outter layers, DP conn fix
2022-11-06 ddr length matching work, misc cleanup
2022-11-19 misc cleanup, change from usb mux to dual uart
2022-11-20 more pcb cleanup, zone work
2022-11-20 add imx8mm 3d model, add FIDs
2022-11-23 change power traces to 0.2mm, misc fixes
2022-11-23 power track thickness fixes, move TPs to back of board
2022-12-18 Rev 1
2023-01-18 misc changes for rev1
2023-01-18 update README with board pics and info
2023-01-18 readme: fix u-boot clone url
2023-01-18 add pdf of rev 1.0 schematics, remove bom.ini
2023-01-20 dsi86: en is active high
2023-02-19 fixup qwiic con p/n, fixup dnp and values based on testing
2023-02-20 update sch datestamp, update schematic pdf
2023-02-26 misc bom cleanup
2023-02-26 reduce board image sizes
2023-05-30 misc bom updates / fixes based on testing
